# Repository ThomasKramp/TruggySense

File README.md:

# TruggySense

This repository contains two generations of the project:

| Folder | Description |
|---|---|
| [`TruggySense_v1`](./TruggySense_v1) | Original system, developed by **[Robbe Elsermans](https://github.com/RobbeElsermans)**. Companion paper: [arXiv:2505.07399](https://arxiv.org/abs/2505.07399) |
| [`TruggySense_v2`](./TruggySense_v2) | Hardware and firmware redesign for reproducibility, developed by **Thomas Kramp**, building on v1 |

Each subfolder has its own README with details on `cad/`, `code/`, and `docs/`.

---

## License

Unless stated otherwise, **original content created for this project** — documentation,
CAD/schematic designs, and project-authored source code — is licensed under
**[CC BY-SA 4.0 (Attribution-ShareAlike 4.0 International)](https://creativecommons.org/licenses/by-sa/4.0/)**.
The full legal text is in [`licence.txt`](./TruggySense_v1/licence.txt) (identical copy also in `TruggySense_v2/`).

In short, if you reuse or build on this work you must:
- **Attribute** the original creator(s) (Robbe Elsermans for v1, Thomas Kramp for v2) and link back to this repository,
- **Indicate any changes** you made,
- **Share any adapted/derivative version under the same license** (CC BY-SA 4.0 or a compatible license).

### What this license does *not* cover

CC BY-SA is intended for creative/documentation works, not for reused third-party software or hardware libraries. The following are **excluded** from the CC BY-SA grant above and remain under their own original licenses/terms:

- **Third-party code libraries** vendored under `code/**/lib/` (e.g. encoder libraries, `TimerInterrupt_Generic`, and similar dependencies pulled in via PlatformIO or copied manually). Check each library's own header/license file or upstream repository before reuse.
- **Vendor-exported component/footprint libraries** under `cad/KiCAD/**` (e.g. `Capture/`, `Quadcept/`, manufacturer `.zip` libraries). These originate from component manufacturers or distributors and are subject to their own terms.
- **Any datasheet, manual, or reference material** included for convenience (e.g. under `docs/`), which remains the property of its original publisher.
- **Trademarks and product names** referenced in this project — including *Team Corally Kagama*, *Teensy*, and other component/brand names — belong to their respective owners. Their use here is purely descriptive (identifying compatible hardware) and does **not** imply affiliation with, sponsorship by, or endorsement from those companies.

If you plan to redistribute or build a product on top of this repository, you are responsible for independently verifying the license terms of any third-party component you rely on.

### Hardware & safety disclaimer

This project involves custom electronics (battery connections, power protection, motor control) built for an RC vehicle platform. It is shared **as-is, for research and educational purposes**:

- No warranty is made regarding the safety, reliability, or fitness of any design for a particular purpose — see the full disclaimer in Section 5 of [`licence.txt`](./TruggySense_v1/licence.txt).
- Building or operating hardware based on this repository (batteries, power electronics, motorized vehicles) carries inherent risk. Do so at your own risk and with appropriate care.
- The authors and Cosys-Lab / University of Antwerp accept no liability for damages, injury, or losses arising from use of this material.

### Note on university/thesis materials

This repository is the output of Master's thesis work supervised by Cosys-Lab. Any university-internal documents (guidelines, templates) are included for context only and remain the property of the University of Antwerp; they are not licensed for reuse under the terms above.

---

## Questions about reuse or licensing

Open an issue on this repository, or reach out via Cosys-Lab, University of Antwerp.

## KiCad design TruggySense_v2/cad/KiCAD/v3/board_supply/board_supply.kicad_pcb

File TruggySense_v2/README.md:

# TruggySense: Hardware and Firmware Redesign for Reproducibility

The continuation of the [TruggySense](https://github.com/Cosys-Lab/TruggySense), that was  originally developed by Robbe Elsermans, a new off-road era of (autonomous) RC-vehicle.

Further developed by Kramp Thomas through Cosys-Lab at University of Antwerp.

Welcome to the readme! A list of what this repo includes

- all files related to the end product,
- source code,
- manuals of the final system.

## cad
Everything related to specialized mounts, holders, and cases to build upon the Team Corally Kagama 1/8 RC vehicle chassis. 
Furthermore, it contains also schematics and circuits drawn in KiCAD.

## code

## docs

## Future perspectives

## licence
BY-SA 4.0 (Attribution-ShareAlike 4.0 International)
See [licence.txt](licence.txt) for the disclaimer

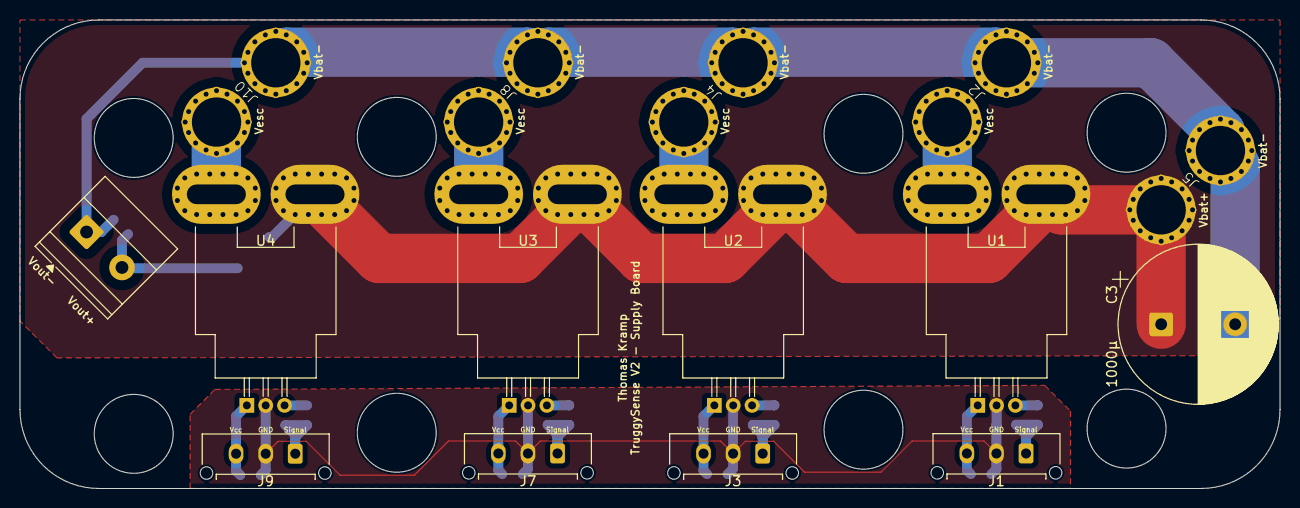
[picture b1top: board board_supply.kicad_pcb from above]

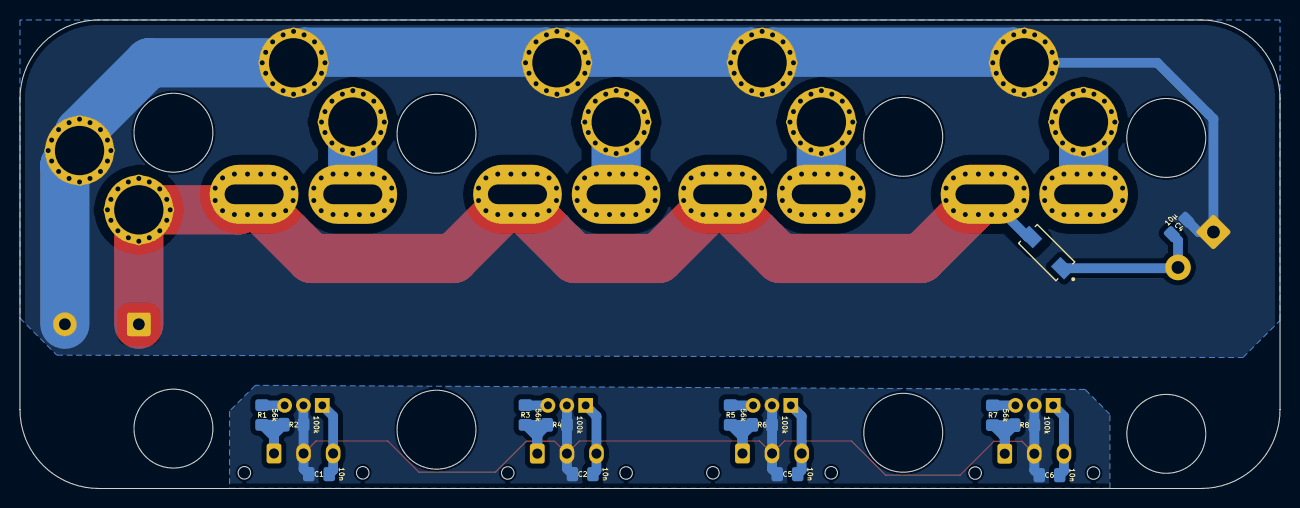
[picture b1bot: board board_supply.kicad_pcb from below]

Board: 6 copper layers, 127.8 x 47.5 mm, 29 parts (14 on the bottom side), 20 nets.

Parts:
C1, C2, C5, C6: 10n; C_0805_2012Metric_Pad1.18x1.45mm_HandSolder
C3: 1000µ; CP_Radial_D16.0mm_P7.50mm
C4: 10µ; C_0805_2012Metric_Pad1.18x1.45mm_HandSolder
D1: VSSAF5M10HM3; DIOM5226X100N
J1, J3, J7, J9: High_I_Sens; Molex_Micro-Fit_3.0_43650-0315_1x03_P3.00mm_Vertical
J2, J4, J8, J10: ESC; EC5_cable_pads
J5: BAT; EC5_cable_pads
J6: TMDC 20-2411; TerminalBlock_Phoenix_MKDS-1,5-2-5.08_1x02_P5.08mm_Horizont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
R1, R3, R5, R7: 56k; R_0805_2012Metric_Pad1.20x1.40mm_HandSolder
R2, R4, R6, R8: 100k; R_0805_2012Metric_Pad1.20x1.40mm_HandSolder
U1, U2, U3, U4: ACS758xCB-200B-PFF; Allegro_CB_PFF

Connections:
+5V_FL: C2.2, J3.3, U2.1 (VCC)
+5V_FR: C1.2, J1.3, U1.1 (VCC)
+5V_RL: C6.2, J9.3, U4.1 (VCC)
+5V_RR: C5.2, J7.3, U3.1 (VCC)
GND: C1.1, C2.1, C5.1, C6.1, J1.2, J3.2, J7.2, J9.2, R2.2, R4.2, R6.2, R8.2, U1.2 (GND), U2.2 (GND), U3.2 (GND), U4.2 (GND)
unnamed: J1.1, R1.2, R2.1
unnamed: J2.1 (V+), U1.5 (IP-)
unnamed: J3.1, R3.2, R4.1
unnamed: J4.1 (V+), U2.5 (IP-)
unnamed: J7.1, R5.2, R6.1
unnamed: J8.1 (V+), U3.5 (IP-)
unnamed: J9.1, R7.2, R8.1
unnamed: J10.1 (V+), U4.5 (IP-)
unnamed: R1.1, U1.3 (VIOUT)
unnamed: R3.1, U2.3 (VIOUT)
unnamed: R5.1, U3.3 (VIOUT)
unnamed: R7.1, U4.3 (VIOUT)
VBAT+: C3.1, D1.2 (A), J5.1 (V+), U1.4 (IP+), U2.4 (IP+), U3.4 (IP+), U4.4 (IP+)
VBAT-: C3.2, C4.2, J2.2 (V-), J4.2 (V-), J5.2 (V-), J6.1, J8.2 (V-), J10.2 (V-)
VTMDC: C4.1, D1.1 (K), J6.2

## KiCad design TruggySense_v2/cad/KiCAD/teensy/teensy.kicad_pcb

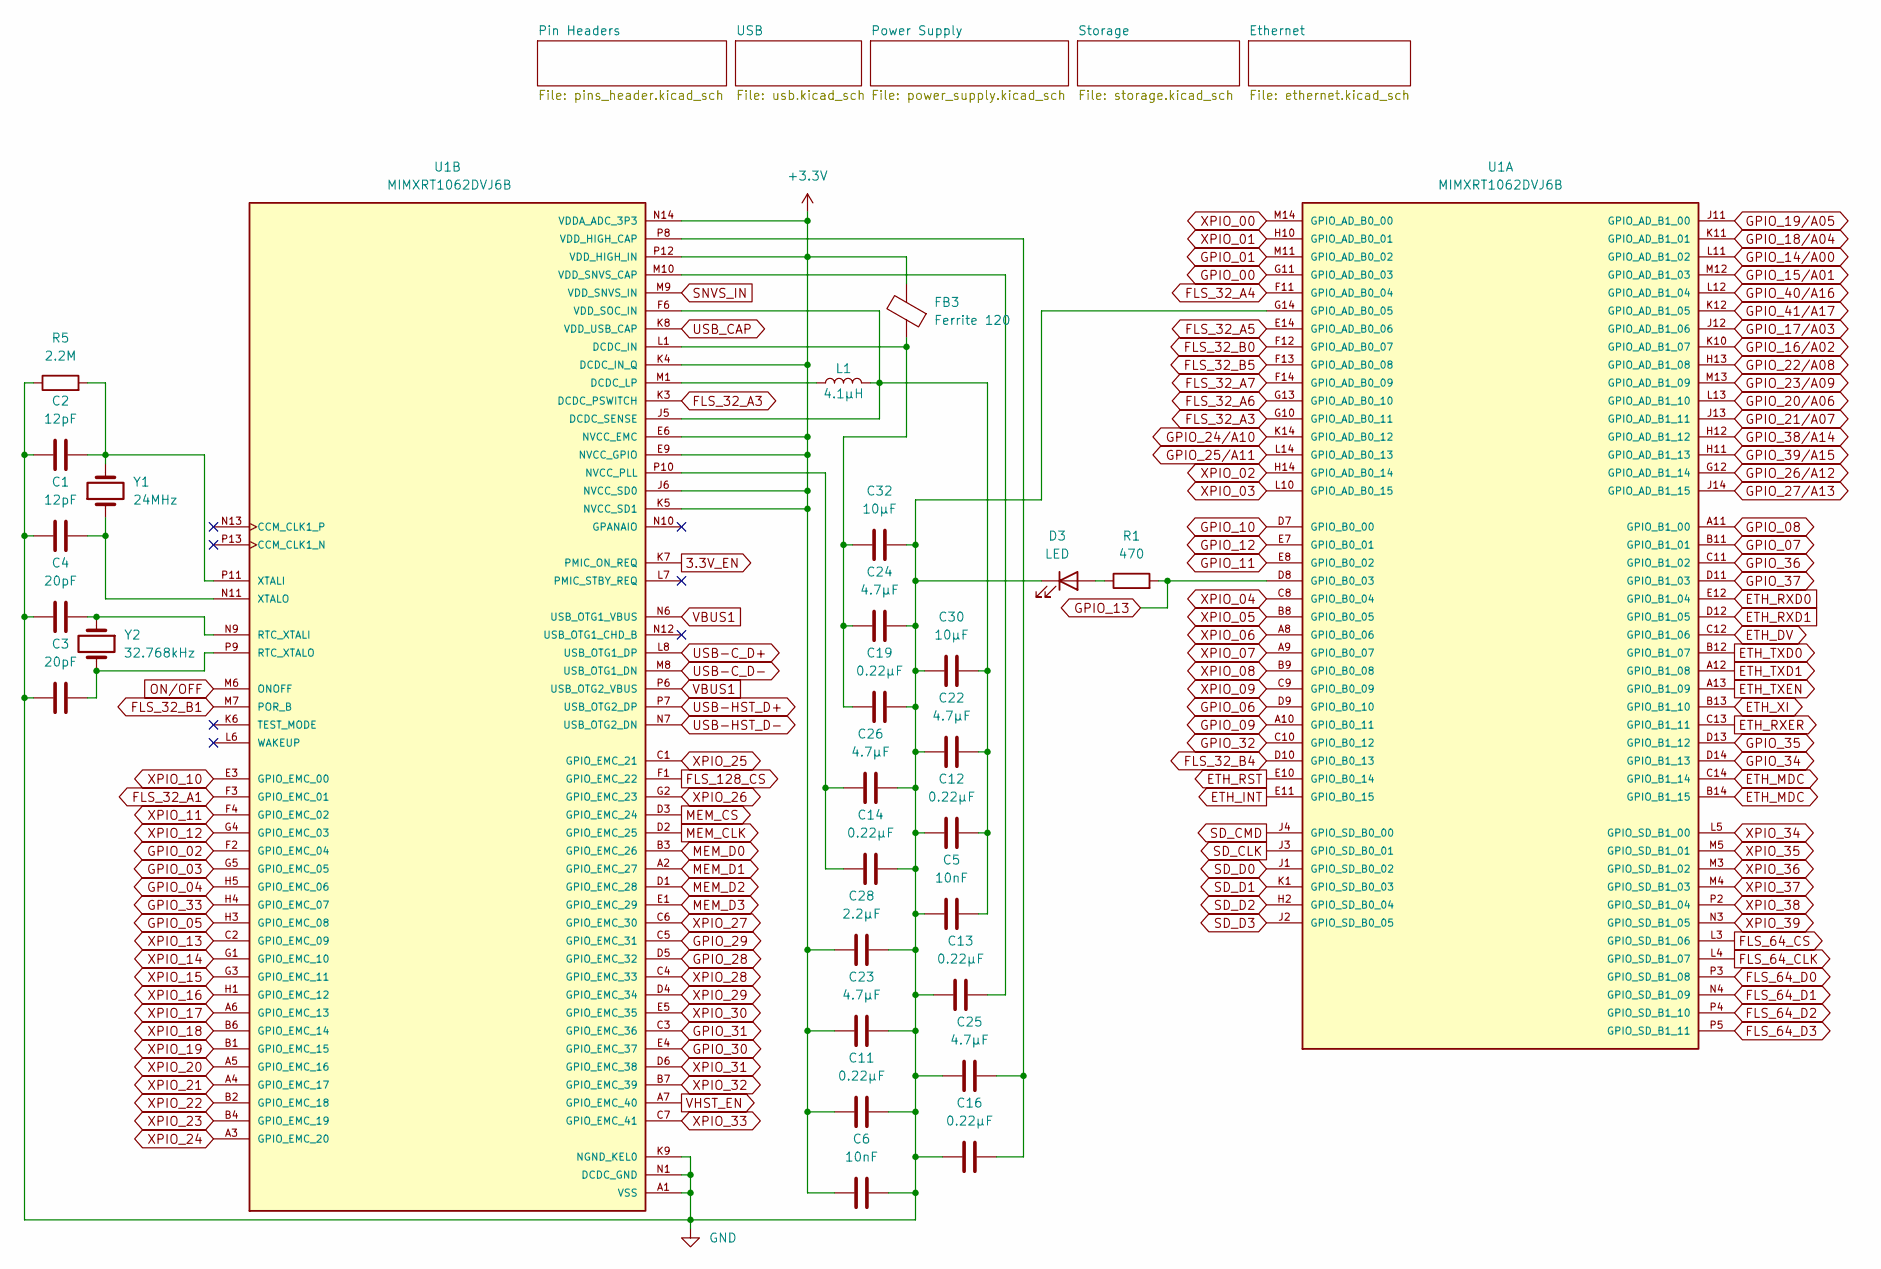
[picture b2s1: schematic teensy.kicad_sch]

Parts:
C1, C2: 12pF; C_0402_1005Metric
C3, C4: 20pF; C_0402_1005Metric
C5, C6: 10nF; C_0402_1005Metric
C11, C12, C13, C14, C16, C19: 0.22µF; C_0402_1005Metric
C22, C23, C24, C25, C26: 4.7µF; C_0603_1608Metric
C28: 2.2µF; C_0603_1608Metric
C30, C32: 10µF; C_0603_1608Metric
D3: LED; LED_0603_1608Metric
FB3: Ferrite 120; L_0603_1608Metric
L1: 4.1µH; L_0603_1608Metric
R1: 470; R_0402_1005Metric
R5: 2.2M; R_0603_1608Metric
U1: MIMXRT1062DVJ6B; BGA196C80P14X14_1200X1200X152N; PARTREV 3
Y1: 24MHz; Crystal_SMD_0603-2Pin_6.0x3.5mm
Y2: 32.768kHz; Crystal_SMD_0603-2Pin_6.0x3.5mm

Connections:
3.3V_EN: U1.K7 (PMIC_ON_REQ); also elsewhere on the board
+3.3V: C6.1, C11.1, C23.1, C28.1, FB3.2, U1.E6 (NVCC_EMC), U1.E9 (NVCC_GPIO), U1.F5 (NVCC_EMC), U1.F10 (NVCC_GPIO), U1.J6 (NVCC_SD0), U1.J10 (NVCC_GPIO), U1.K4 (DCDC_IN_Q), U1.K5 (NVCC_SD1), U1.N14 (VDDA_ADC_3P3), U1.P12 (VDD_HIGH_IN); also elsewhere on the board
DCDC_IN: C19.1, C24.1, C32.1, FB3.1, U1.L1 (DCDC_IN), U1.L2 (DCDC_IN)
DCDC_LP: L1.1, U1.M1 (DCDC_LP), U1.M2 (DCDC_LP)
ETH_DV: U1.C12 (GPIO_B1_06); also elsewhere on the board
ETH_INT: U1.E11 (GPIO_B0_15); also elsewhere on the board
ETH_MDC: U1.B14 (GPIO_B1_15), U1.C14 (GPIO_B1_14); also elsewhere on the board
ETH_RST: U1.E10 (GPIO_B0_14); also elsewhere on the board
ETH_RXD0: U1.E12 (GPIO_B1_04); also elsewhere on the board
ETH_RXD1: U1.D12 (GPIO_B1_05); also elsewhere on the board
ETH_RXER: U1.C13 (GPIO_B1_11); also elsewhere on the board
ETH_TXD0: U1.B12 (GPIO_B1_07); also elsewhere on the board
ETH_TXD1: U1.A12 (GPIO_B1_08); also elsewhere on the board
ETH_TXEN: U1.A13 (GPIO_B1_09); also elsewhere on the board
ETH_XI: U1.B13 (GPIO_B1_10); also elsewhere on the board
FLS_32_A1: U1.F3 (GPIO_EMC_01); also elsewhere on the board
FLS_32_A3: U1.G10 (GPIO_AD_B0_11), U1.K3 (DCDC_PSWITCH); also elsewhere on the board
FLS_32_A4: U1.F11 (GPIO_AD_B0_04); also elsewhere on the board
FLS_32_A5: U1.E14 (GPIO_AD_B0_06); also elsewhere on the board
FLS_32_A6: U1.G13 (GPIO_AD_B0_10); also elsewhere on the board
FLS_32_A7: U1.F14 (GPIO_AD_B0_09); also elsewhere on the board
FLS_32_B0: U1.F12 (GPIO_AD_B0_07); also elsewhere on the board
FLS_32_B1: U1.M7 (POR_B); also elsewhere on the board
FLS_32_B4: U1.D10 (GPIO_B0_13); also elsewhere on the board
FLS_32_B5: U1.F13 (GPIO_AD_B0_08); also elsewhere on the board
FLS_64_CLK: U1.L4 (GPIO_SD_B1_07); also elsewhere on the board
FLS_64_CS: U1.L3 (GPIO_SD_B1_06); also elsewhere on the board
FLS_64_D0: U1.P3 (GPIO_SD_B1_08); also elsewhere on the board
FLS_64_D1: U1.N4 (GPIO_SD_B1_09); also elsewhere on the board
FLS_64_D2: U1.P4 (GPIO_SD_B1_10); also elsewhere on the board
FLS_64_D3: U1.P5 (GPIO_SD_B1_11); also elsewhere on the board
FLS_128_CS: U1.F1 (GPIO_EMC_22); also elsewhere on the board
GND: C1.1, C2.1, C3.1, C4.1, C5.1, C6.2, C11.2, C12.1, C13.1, C14.2, C16.1, C19.2, C22.1, C23.2, C24.2, C25.1, C26.2, C28.2, C30.1, C32.2, D3.1 (K), R5.1, U1.A1 (VSS), U1.A14 (VSS), U1.B5 (VSS), U1.B10 (VSS), U1.E2 (VSS), U1.E13 (VSS), U1.G7 (VSS), U1.G8 (VSS), U1.G14 (GPIO_AD_B0_05), U1.H7 (VSS), U1.H8 (VSS), U1.J7 (VSS), U1.J8 (VSS), U1.K2 (VSS), U1.K9 (NGND_KEL0), U1.K13 (VSS), U1.L9 (VSS), U1.N1 (DCDC_GND), U1.N2 (DCDC_GND), U1.N5 (VSS), U1.N8 (VSS), U1.P1 (VSS), U1.P14 (VSS); also elsewhere on the board
GPIO_00: U1.G11 (GPIO_AD_B0_03); also elsewhere on the board
GPIO_01: U1.M11 (GPIO_AD_B0_02); also elsewhere on the board
GPIO_02: U1.F2 (GPIO_EMC_04); also elsewhere on the board
GPIO_03: U1.G5 (GPIO_EMC_05); also elsewhere on the board
GPIO_04: U1.H5 (GPIO_EMC_06); also elsewhere on the board
GPIO_05: U1.H3 (GPIO_EMC_08); also elsewhere on the board
GPIO_06: U1.D9 (GPIO_B0_10); also elsewhere on the board
GPIO_07: U1.B11 (GPIO_B1_01); also elsewhere on the board
GPIO_08: U1.A11 (GPIO_B1_00); also elsewhere on the board
GPIO_09: U1.A10 (GPIO_B0_11); also elsewhere on the board
GPIO_10: U1.D7 (GPIO_B0_00); also elsewhere on the board
GPIO_11: U1.E8 (GPIO_B0_02); also elsewhere on the board
GPIO_12: U1.E7 (GPIO_B0_01); also elsewhere on the board
GPIO_13: R1.2, U1.D8 (GPIO_B0_03); also elsewhere on the board
GPIO_14/A00: U1.L11 (GPIO_AD_B1_02); also elsewhere on the board
GPIO_15/A01: U1.M12 (GPIO_AD_B1_03); also elsewhere on the board
GPIO_16/A02: U1.K10 (GPIO_AD_B1_07); also elsewhere on the board
GPIO_17/A03: U1.J12 (GPIO_AD_B1_06); also elsewhere on the board
GPIO_18/A04: U1.K11 (GPIO_AD_B1_01); also elsewhere on the board
GPIO_19/A05: U1.J11 (GPIO_AD_B1_00); also elsewhere on the board
GPIO_20/A06: U1.L13 (GPIO_AD_B1_10); also elsewhere on the board
GPIO_21/A07: U1.J13 (GPIO_AD_B1_11); also elsewhere on the board
GPIO_22/A08: U1.H13 (GPIO_AD_B1_08); also elsewhere on the board
GPIO_23/A09: U1.M13 (GPIO_AD_B1_09); also elsewhere on the board
GPIO_24/A10: U1.K14 (GPIO_AD_B0_12); also elsewhere on the board
GPIO_25/A11: U1.L14 (GPIO_AD_B0_13); also elsewhere on the board
GPIO_26/A12: U1.G12 (GPIO_AD_B1_14); also elsewhere on the board
GPIO_27/A13: U1.J14 (GPIO_AD_B1_15); also elsewhere on the board
GPIO_28: U1.D5 (GPIO_EMC_32); also elsewhere on the board
GPIO_29: U1.C5 (GPIO_EMC_31); also elsewhere on the board
GPIO_30: U1.E4 (GPIO_EMC_37); also elsewhere on the board
GPIO_31: U1.C3 (GPIO_EMC_36); also elsewhere on the board
GPIO_32: U1.C10 (GPIO_B0_12); also elsewhere on the board
GPIO_33: U1.H4 (GPIO_EMC_07); also elsewhere on the board
GPIO_34: U1.D14 (GPIO_B1_13); also elsewhere on the board
GPIO_35: U1.D13 (GPIO_B1_12); also elsewhere on the board
GPIO_36: U1.C11 (GPIO_B1_02); also elsewhere on the board
GPIO_37: U1.D11 (GPIO_B1_03); also elsewhere on the board
GPIO_38/A14: U1.H12 (GPIO_AD_B1_12); also elsewhere on the board
GPIO_39/A15: U1.H11 (GPIO_AD_B1_13); also elsewhere on the board
GPIO_40/A16: U1.L12 (GPIO_AD_B1_04); also elsewhere on the board
GPIO_41/A17: U1.K12 (GPIO_AD_B1_05); also elsewhere on the board
MEM_CLK: U1.D2 (GPIO_EMC_25); also elsewhere on the board
MEM_CS: U1.D3 (GPIO_EMC_24); also elsewhere on the board
MEM_D0: U1.B3 (GPIO_EMC_26); also elsewhere on the board
MEM_D1: U1.A2 (GPIO_EMC_27); also elsewhere on the board
MEM_D2: U1.D1 (GPIO_EMC_28); also elsewhere on the board
MEM_D3: U1.E1 (GPIO_EMC_29); also elsewhere on the board
unnamed: D3.2 (A), R1.1
unnamed: C14.1, C26.1, U1.P10 (NVCC_PLL)
unnamed: C4.2, U1.N9 (RTC_XTALI), Y2.1
unnamed: C3.2, U1.P9 (RTC_XTALO), Y2.2
unnamed: C16.2, C25.2, U1.P8 (VDD_HIGH_CAP)
unnamed: C13.2, U1.M10 (VDD_SNVS_CAP)
unnamed: C2.2, R5.2, U1.P11 (XTALI), Y1.2
unnamed: C1.2, U1.N11 (XTALO), Y1.1
ON/OFF: U1.M6 (ONOFF); also elsewhere on the board
SD_CLK: U1.J3 (GPIO_SD_B0_01); also elsewhere on the board
SD_CMD: U1.J4 (GPIO_SD_B0_00); also elsewhere on the board
SD_D0: U1.J1 (GPIO_SD_B0_02); also elsewhere on the board
SD_D1: U1.K1 (GPIO_SD_B0_03); also elsewhere on the board
SD_D2: U1.H2 (GPIO_SD_B0_04); also elsewhere on the board
SD_D3: U1.J2 (GPIO_SD_B0_05); also elsewhere on the board
SNVS_IN: U1.M9 (VDD_SNVS_IN); also elsewhere on the board
USB-C_D+: U1.L8 (USB_OTG1_DP); also elsewhere on the board
USB-C_D-: U1.M8 (USB_OTG1_DN); also elsewhere on the board
USB-HST_D+: U1.P7 (USB_OTG2_DP); also elsewhere on the board
USB-HST_D-: U1.N7 (USB_OTG2_DN); also elsewhere on the board
USB_CAP: U1.K8 (VDD_USB_CAP); also elsewhere on the board
VBUS1: U1.N6 (USB_OTG1_VBUS), U1.P6 (USB_OTG2_VBUS); also elsewhere on the board
VDD_SOC_IN: C5.2, C12.2, C22.2, C30.2, L1.2, U1.F6 (VDD_SOC_IN), U1.F7 (VDD_SOC_IN), U1.F8 (VDD_SOC_IN), U1.F9 (VDD_SOC_IN), U1.G6 (VDD_SOC_IN), U1.G9 (VDD_SOC_IN), U1.H6 (VDD_SOC_IN), U1.H9 (VDD_SOC_IN), U1.J5 (DCDC_SENSE), U1.J9 (VDD_SOC_IN)
VHST_EN: U1.A7 (GPIO_EMC_40); also elsewhere on the board
XPIO_00: U1.M14 (GPIO_AD_B0_00); also elsewhere on the board
XPIO_01: U1.H10 (GPIO_AD_B0_01); also elsewhere on the board
XPIO_02: U1.H14 (GPIO_AD_B0_14); also elsewhere on the board
XPIO_03: U1.L10 (GPIO_AD_B0_15); also elsewhere on the board
XPIO_04: U1.C8 (GPIO_B0_04); also elsewhere on the board
XPIO_05: U1.B8 (GPIO_B0_05); also elsewhere on the board
XPIO_06: U1.A8 (GPIO_B0_06); also elsewhere on the board
XPIO_07: U1.A9 (GPIO_B0_07); also elsewhere on the board
XPIO_08: U1.B9 (GPIO_B0_08); also elsewhere on the board
XPIO_09: U1.C9 (GPIO_B0_09); also elsewhere on the board
XPIO_10: U1.E3 (GPIO_EMC_00); also elsewhere on the board
XPIO_11: U1.F4 (GPIO_EMC_02); also elsewhere on the board
XPIO_12: U1.G4 (GPIO_EMC_03); also elsewhere on the board
XPIO_13: U1.C2 (GPIO_EMC_09); also elsewhere on the board
XPIO_14: U1.G1 (GPIO_EMC_10); also elsewhere on the board
XPIO_15: U1.G3 (GPIO_EMC_11); also elsewhere on the board
XPIO_16: U1.H1 (GPIO_EMC_12); also elsewhere on the board
XPIO_17: U1.A6 (GPIO_EMC_13); also elsewhere on the board
XPIO_18: U1.B6 (GPIO_EMC_14); also elsewhere on the board
XPIO_19: U1.B1 (GPIO_EMC_15); also elsewhere on the board
XPIO_20: U1.A5 (GPIO_EMC_16); also elsewhere on the board
XPIO_21: U1.A4 (GPIO_EMC_17); also elsewhere on the board
XPIO_22: U1.B2 (GPIO_EMC_18); also elsewhere on the board
XPIO_23: U1.B4 (GPIO_EMC_19); also elsewhere on the board
XPIO_24: U1.A3 (GPIO_EMC_20); also elsewhere on the board
XPIO_25: U1.C1 (GPIO_EMC_21); also elsewhere on the board
XPIO_26: U1.G2 (GPIO_EMC_23); also elsewhere on the board
XPIO_27: U1.C6 (GPIO_EMC_30); also elsewhere on the board
XPIO_28: U1.C4 (GPIO_EMC_33); also elsewhere on the board
XPIO_29: U1.D4 (GPIO_EMC_34); also elsewhere on the board
XPIO_30: U1.E5 (GPIO_EMC_35); also elsewhere on the board
XPIO_31: U1.D6 (GPIO_EMC_38); also elsewhere on the board
XPIO_32: U1.B7 (GPIO_EMC_39); also elsewhere on the board
XPIO_33: U1.C7 (GPIO_EMC_41); also elsewhere on the board
XPIO_34: U1.L5 (GPIO_SD_B1_00); also elsewhere on the board
XPIO_35: U1.M5 (GPIO_SD_B1_01); also elsewhere on the board
XPIO_36: U1.M3 (GPIO_SD_B1_02); also elsewhere on the board
XPIO_37: U1.M4 (GPIO_SD_B1_03); also elsewhere on the board
XPIO_38: U1.P2 (GPIO_SD_B1_04); also elsewhere on the board
XPIO_39: U1.N3 (GPIO_SD_B1_05); also elsewhere on the board

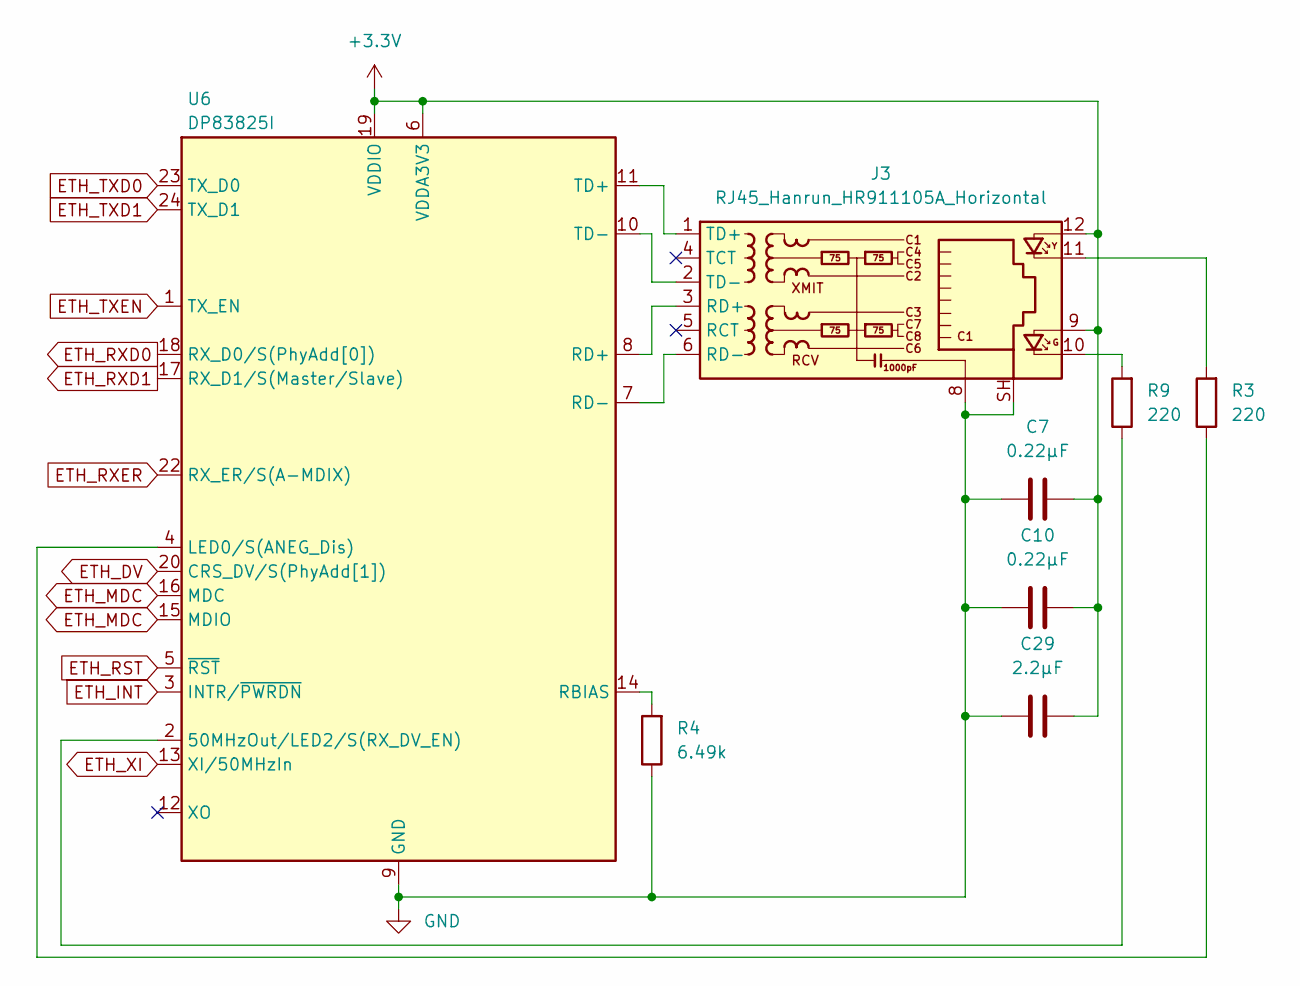
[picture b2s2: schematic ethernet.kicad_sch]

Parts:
C7, C10: 0.22µF; C_0402_1005Metric
C29: 2.2µF; C_0603_1608Metric
J3: RJ45_Hanrun_HR911105A_Horizontal
R3, R9: 220; R_0402_1005Metric
R4: 6.49k; R_0402_1005Metric
U6: DP83825I; Texas_RMQ0024A_WQFN-24-1EP_3x3mm_P0.4mm_EP1.9x1.9mm

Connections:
+3.3V: C7.2, C10.2, C29.2, J3.9, J3.12, U6.6 (VDDA3V3), U6.19 (VDDIO); also elsewhere on the board
ETH_DV: U6.20 (CRS_DV/S(PhyAdd[1])); also elsewhere on the board
ETH_INT: U6.3 (INTR/~PWRDN); also elsewhere on the board
ETH_MDC: U6.15 (MDIO), U6.16 (MDC); also elsewhere on the board
ETH_RST: U6.5 (~RST); also elsewhere on the board
ETH_RXD0: U6.18 (RX_D0/S(PhyAdd[0])); also elsewhere on the board
ETH_RXD1: U6.17 (RX_D1/S(Master/Slave)); also elsewhere on the board
ETH_RXER: U6.22 (RX_ER/S(A-MDIX)); also elsewhere on the board
ETH_TXD0: U6.23 (TX_D0); also elsewhere on the board
ETH_TXD1: U6.24 (TX_D1); also elsewhere on the board
ETH_TXEN: U6.1 (TX_EN); also elsewhere on the board
ETH_XI: U6.13 (XI/50MHzIn); also elsewhere on the board
GND: C7.1, C10.1, C29.1, J3.8, J3.SH, R4.1, U6.9 (GND), U6.21 (GND), U6.25 (GND); also elsewhere on the board
unnamed: J3.10, R9.2
unnamed: J3.11, R3.2
unnamed: J3.3 (RD+), U6.8 (RD+)
unnamed: J3.6 (RD-), U6.7 (RD-)
unnamed: J3.1 (TD+), U6.11 (TD+)
unnamed: J3.2 (TD-), U6.10 (TD-)
unnamed: R9.1, U6.2 (50MHzOut/LED2/S(RX_DV_EN))
unnamed: R3.1, U6.4 (LED0/S(ANEG_Dis))
unnamed: R4.2, U6.14 (RBIAS)

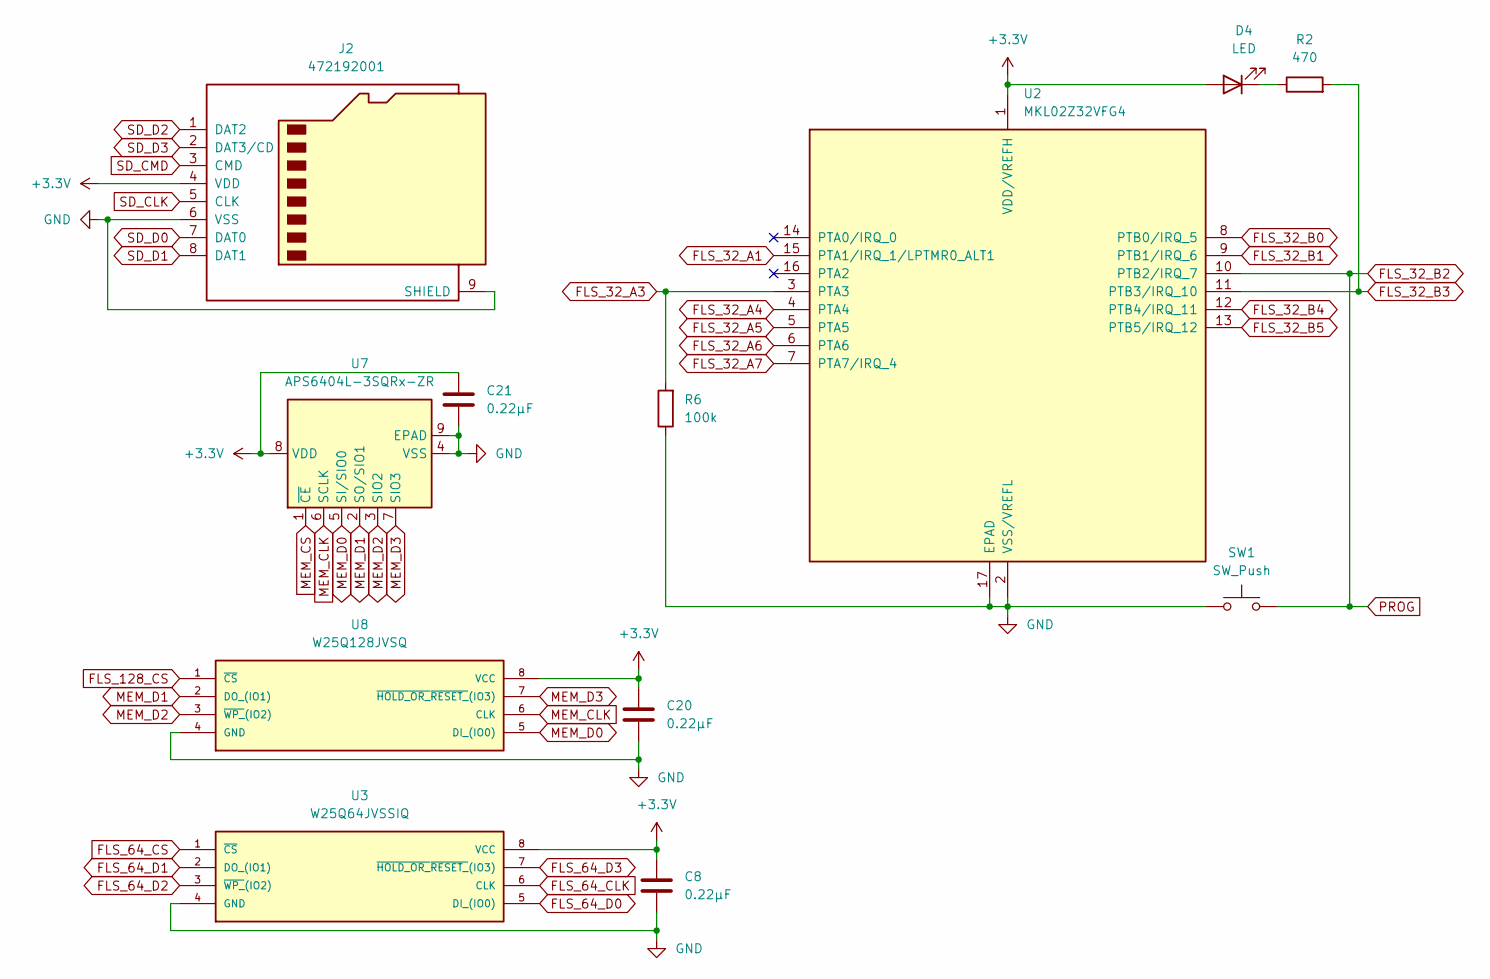
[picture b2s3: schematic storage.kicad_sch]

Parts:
C8, C20, C21: 0.22µF; C_0402_1005Metric
D4: LED; LED_0603_1608Metric
J2: 472192001; microSD_HC_Molex_47219-2001
R2: 470; R_0402_1005Metric
R6: 100k; R_0603_1608Metric
SW1: SW_Push; SW_SPST_EVQP2_MiddlePushTravel_H2.5mm
U2: MKL02Z32VFG4; QFN-16-1EP_3x3mm_P0.5mm_EP1.9x1.9mm
U3: W25Q64JVSSIQ; SOIC127P790X216-8N; MANUFACTURER_PART_NUMBER W25Q64JVSSIQ
U7: APS6404L-3SQRx-ZR; Winbond_USON-8-1EP_3x2mm_P0.5mm_EP0.2x1.6mm
U8: W25Q128JVSQ; SOIC127P790X216-8N; MANUFACTURER_PART_NUMBER W25Q128JVSQ

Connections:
+3.3V: C8.1, C20.1, C21.1, D4.2 (A), J2.4 (VDD), U2.1 (VDD/VREFH), U3.8 (VCC), U7.8 (VDD), U8.8 (VCC); also elsewhere on the board
FLS_32_A1: U2.15 (PTA1/IRQ_1/LPTMR0_ALT1); also elsewhere on the board
FLS_32_A3: R6.2, U2.3 (PTA3); also elsewhere on the board
FLS_32_A4: U2.4 (PTA4); also elsewhere on the board
FLS_32_A5: U2.5 (PTA5); also elsewhere on the board
FLS_32_A6: U2.6 (PTA6); also elsewhere on the board
FLS_32_A7: U2.7 (PTA7/IRQ_4); also elsewhere on the board
FLS_32_B0: U2.8 (PTB0/IRQ_5); also elsewhere on the board
FLS_32_B1: U2.9 (PTB1/IRQ_6); also elsewhere on the board
FLS_32_B2: SW1.2, U2.10 (PTB2/IRQ_7); also elsewhere on the board
FLS_32_B3: R2.2, U2.11 (PTB3/IRQ_10)
FLS_32_B4: U2.12 (PTB4/IRQ_11); also elsewhere on the board
FLS_32_B5: U2.13 (PTB5/IRQ_12); also elsewhere on the board
FLS_64_CLK: U3.6 (CLK); also elsewhere on the board
FLS_64_CS: U3.1 (~CS); also elsewhere on the board
FLS_64_D0: U3.5 (DI_(IO0)); also elsewhere on the board
FLS_64_D1: U3.2 (DO_(IO1)); also elsewhere on the board
FLS_64_D2: U3.3 (~WP_(IO2)); also elsewhere on the board
FLS_64_D3: U3.7 (~HOLD_OR_~RESET_(IO3)); also elsewhere on the board
FLS_128_CS: U8.1 (~CS); also elsewhere on the board
GND: C8.2, C20.2, C21.2, J2.6 (VSS), J2.9 (SHIELD), R6.1, SW1.1, U2.2 (VSS/VREFL), U2.17 (EPAD), U3.4 (GND), U7.4 (VSS), U7.9 (EPAD), U8.4 (GND); also elsewhere on the board
MEM_CLK: U7.6 (SCLK), U8.6 (CLK); also elsewhere on the board
MEM_CS: U7.1 (~CE); also elsewhere on the board
MEM_D0: U7.5 (SI/SIO0), U8.5 (DI_(IO0)); also elsewhere on the board
MEM_D1: U7.2 (SO/SIO1), U8.2 (DO_(IO1)); also elsewhere on the board
MEM_D2: U7.3 (SIO2), U8.3 (~WP_(IO2)); also elsewhere on the board
MEM_D3: U7.7 (SIO3), U8.7 (~HOLD_OR_~RESET_(IO3)); also elsewhere on the board
unnamed: D4.1 (K), R2.1
SD_CLK: J2.5 (CLK); also elsewhere on the board
SD_CMD: J2.3 (CMD); also elsewhere on the board
SD_D0: J2.7 (DAT0); also elsewhere on the board
SD_D1: J2.8 (DAT1); also elsewhere on the board
SD_D2: J2.1 (DAT2); also elsewhere on the board
SD_D3: J2.2 (DAT3/CD); also elsewhere on the board

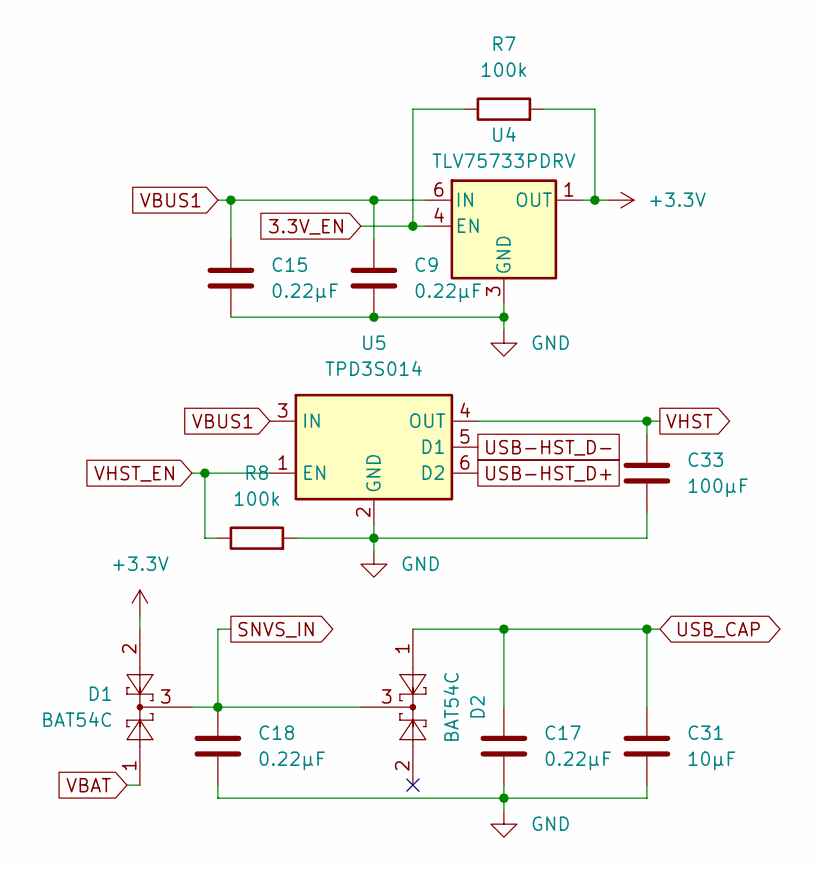
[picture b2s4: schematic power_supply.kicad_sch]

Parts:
C9, C15, C17, C18: 0.22µF; C_0402_1005Metric
C31: 10µF; C_0603_1608Metric
C33: 100µF; C_0603_1608Metric
D1, D2: BAT54C; SOT-23
R7, R8: 100k; R_0603_1608Metric
U4: TLV75733PDRV; WSON-6-1EP_2x2mm_P0.65mm_EP1x1.6mm
U5: TPD3S014; SOT-23-6

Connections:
3.3V_EN: R7.1, U4.4 (EN); also elsewhere on the board
+3.3V: D1.2, R7.2, U4.1 (OUT); also elsewhere on the board
GND: C9.2, C15.2, C17.1, C18.2, C31.1, C33.2, R8.2, U4.3 (GND), U4.7 (GND), U5.2 (GND); also elsewhere on the board
SNVS_IN: C18.1, D1.3, D2.3; also elsewhere on the board
USB-HST_D+: U5.6 (D2); also elsewhere on the board
USB-HST_D-: U5.5 (D1); also elsewhere on the board
USB_CAP: C17.2, C31.2, D2.1; also elsewhere on the board
VBAT: D1.1; also elsewhere on the board
VBUS1: C9.1, C15.1, U4.6 (IN), U5.3 (IN); also elsewhere on the board
VHST: C33.1, U5.4 (OUT); also elsewhere on the board
VHST_EN: R8.1, U5.1 (EN); also elsewhere on the board

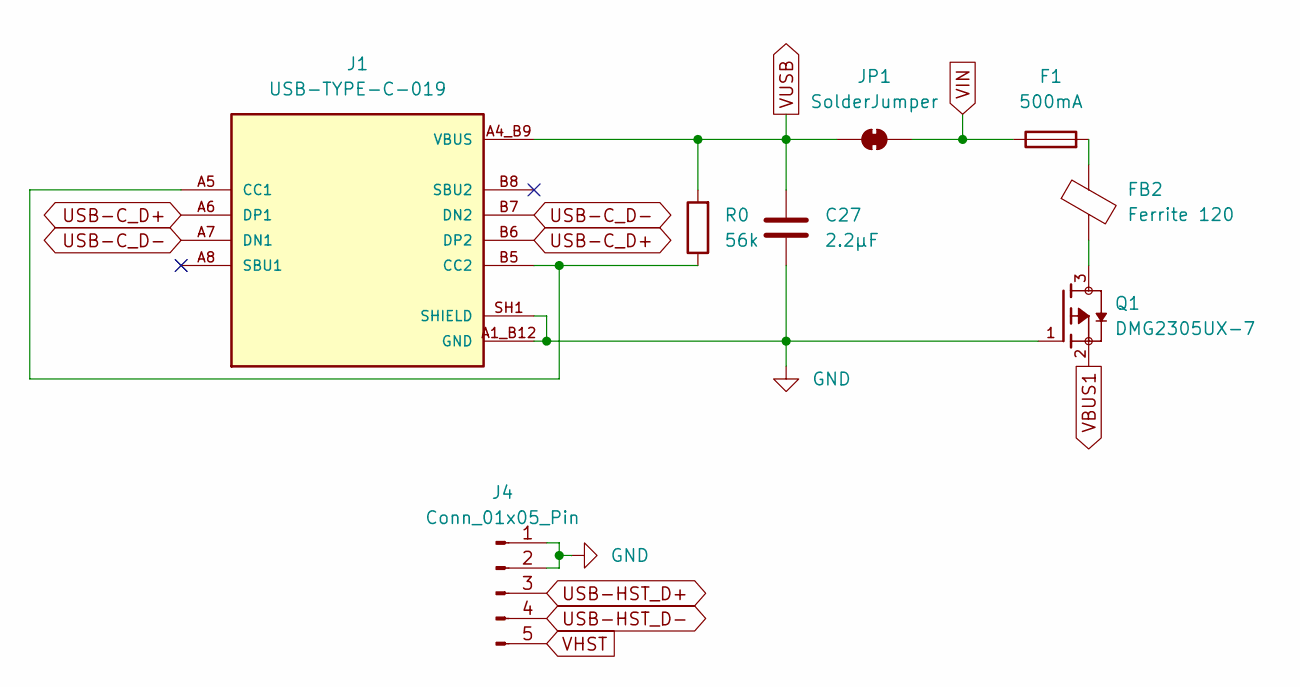
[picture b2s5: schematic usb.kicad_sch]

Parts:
C27: 2.2µF; C_0603_1608Metric
F1: 500mA; Fuse_0603_1608Metric
FB2: Ferrite 120; L_0603_1608Metric
J1: USB-TYPE-C-019; AMPHENOL_10155435-00031LF; PARTREV C
J4: Conn_01x05_Pin; PinHeader_1x05_P2.54mm_Vertical
JP1: SolderJumper; SolderJumper-2_P1.3mm_Open_TrianglePad1.0x1.5mm
Q1: DMG2305UX-7; SOT91P240X110-3N_DMG2305UX-7; PARTREV 09/2018
R0: 56k; R_0603_1608Metric

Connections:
GND: C27.1, J1.A1_B12 (GND), J1.B1_A12 (GND), J1.SH1 (SHIELD), J1.SH2 (SHIELD), J1.SH3 (SHIELD), J1.SH4 (SHIELD), J4.1, J4.2, Q1.1; also elsewhere on the board
unnamed: F1.2, FB2.1
unnamed: FB2.2, Q1.3
unnamed: J1.A5 (CC1), J1.B5 (CC2), R0.1
USB-C_D+: J1.A6 (DP1), J1.B6 (DP2); also elsewhere on the board
USB-C_D-: J1.A7 (DN1), J1.B7 (DN2); also elsewhere on the board
USB-HST_D+: J4.3; also elsewhere on the board
USB-HST_D-: J4.4; also elsewhere on the board
VBUS1: Q1.2; also elsewhere on the board
VHST: J4.5; also elsewhere on the board
VIN: F1.1, JP1.2 (B); also elsewhere on the board
VUSB: C27.2, J1.A4_B9 (VBUS), J1.B4_A9 (VBUS), JP1.1 (A), R0.2; also elsewhere on the board
